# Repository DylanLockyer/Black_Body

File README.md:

# Black Body Controller
[USER MANUAL](Documentation/README.md)

## Overview
This project controls and monitors a black body heater module mounted to the 4K stage of a cryostat. It is split into two custom PCBs: a heater control board built around an ESP32 (current source, voltage/current sensing, PID control, and a self-hosted web interface) and a temperature sensor board built around an STM32G4 for reading from a germanium temperature sensor for ranges from 0.3 to 100 kelvin (high-precision, low-noise excitation and readout for temperature probes). The two boards communicate over SPI, with the ESP32 acting as the master controller and network-facing interface.

## Project Goals
- Heat the black body module (4x 10Ω heaters in series, 40Ω equivalent) from the cryostat's 4K stage to temperatures above 80K, with closed-loop PID control.
- Accurately measure temperature across the cryogenic range using a Germanium RTD (LakeShore GR-300-AA).
- Provide low-noise, precisely switchable current excitation (10nA to 1mA) and high-resolution (24-bit) voltage/current measurement for sensor readout.
- Expose a self-hosted web interface (over WiFi) for live monitoring and control of both heating and measurement, with no external software required.

## Documentation
- [Heater Control PCB](Circuit%20Boards/Black_Body_Heater_Control_PCB/README.md) — heater current source, voltage/current sensing, and power supply design.
- [Temperature Sensor PCB](Circuit%20Boards/Black_Body_Temperature_Sensor_PCB/README.md) — sensor excitation, precision measurement, and isolation design.
- [ESP32 Firmware](Firmware/ESP32_heater/README.md) — heater PID control, SPI link to the sensor board, and the web interface.
- [STM32 Firmware](Firmware/stm32_black_body/README.md) — sensor excitation control, ADC readout, and the SPI link to the ESP32.
- [Device Usage Guide](Documentation/README.md) — how to power up, connect to, and operate the device.

## Repository Organization
**Circuit Boards:** KiCad source files and manufacturing/gerber files for both PCBs.

**Firmware:** ESP32 (PlatformIO) heater control firmware and STM32 (STM32CubeIDE) sensor readout firmware.

**Documentation:** Images, schematics, and the device usage guide.

**Simulations:** LTspice and PSpice simulations used to validate circuit designs before ordering.

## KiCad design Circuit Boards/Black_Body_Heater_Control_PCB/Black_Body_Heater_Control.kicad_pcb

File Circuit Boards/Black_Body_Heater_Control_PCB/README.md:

# Black Body Heater Control PCB

Two-layer circuit board carrying the ESP32 microcontroller and all heater control electronics: current source, voltage/current sensing, and power supply. See the [firmware README](../../Firmware/ESP32_heater/README.md) for how this board is driven, and the [root README](../../README.md) for overall project context.

Schematic: [Black_Body_Heater_Control_Schematic.pdf](../Black_Body_Heater_Control_Schematic.pdf)

## Microcontroller
An ESP32 was chosen for its high pin count and WiFi support, letting it self-host a web page for displaying readings and controlling the heater. It interfaces with the [temperature sensor board](../Black_Body_Temperature_Sensor_PCB/README.md) over SPI (3 CS lines for 3 temperature probes). The microcontroller is programmed over USB, with exposed pads for UART programming as a fallback. Board-to-board interfacing uses Molex connectors (504050-0891 for the SPI link) since they could be sampled for free.

## Heater Controller
The heater is 4x 10Ω resistors in series (40Ω total). A maximum output power of 10W requires a peak 12V at 0.3A, measured with a shunt resistor + amplifier (current) and a voltage divider (voltage), both read by the ESP32's internal 12-bit ADC. This gives a theoretical current step of 100µA (max 0.66A range) and a voltage step of 8mV (max 36V range).

The original design used an N-channel MOSFET with PWM to control heater voltage. Due to concerns about PWM noise interfering with the sensor board's measurements, this was replaced with an analog current source instead.

Output current vs. input voltage for the analog current source. A BJT and op-amp generate the current output, driven by a DAC that the microcontroller controls.

## Shunt Current Measurement
The shunt resistor is 100mΩ with a 50V/V amplifier gain, giving 2.5V output at 0.5A and 0.25V at 0.05A. A low-pass filter on the amplifier output is largely unnecessary now that PWM isn't used, but is kept (with an easy jumper to bypass it) in case it's needed. Simulated filtering of a 10% duty cycle, 10kHz PWM signal on 20V is shown below:

## Power Source
The board receives 12V from an external power supply. A buck converter steps this down to 5V at 2A, followed by an LDO to 3.3V for a clean, low-noise supply to the microcontroller and ADC. \
**Revision 1:** Changed buck converter to newer module as the rev 0 as it broke and fried both boards.

## Simulation
Heater and buck converter behavior were validated in PSpice before layout (see [Simulations/Heater_Controller_PCB](../../Simulations/Heater_Controller_PCB)):

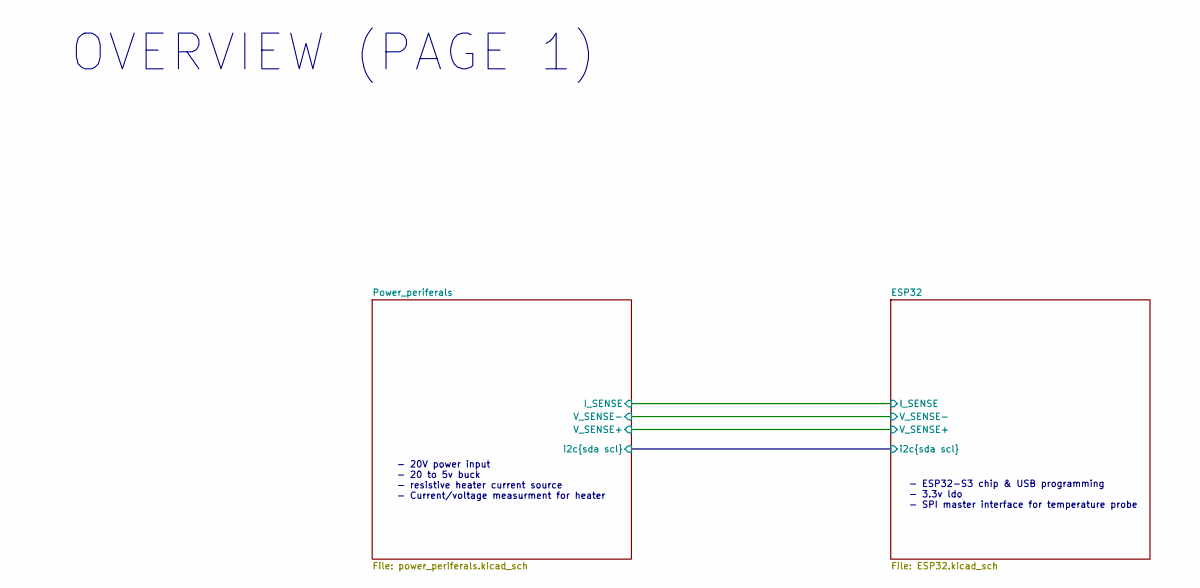
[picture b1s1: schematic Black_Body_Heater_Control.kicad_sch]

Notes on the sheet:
OVERVIEW (PAGE 1)
- ESP32-S3 chip & USB programming - 3.3v ldo - SPI master interface for temperature probe
- 20V power input - 20 to 5v buck - resistive heater current source - Current/voltage measurment for heater

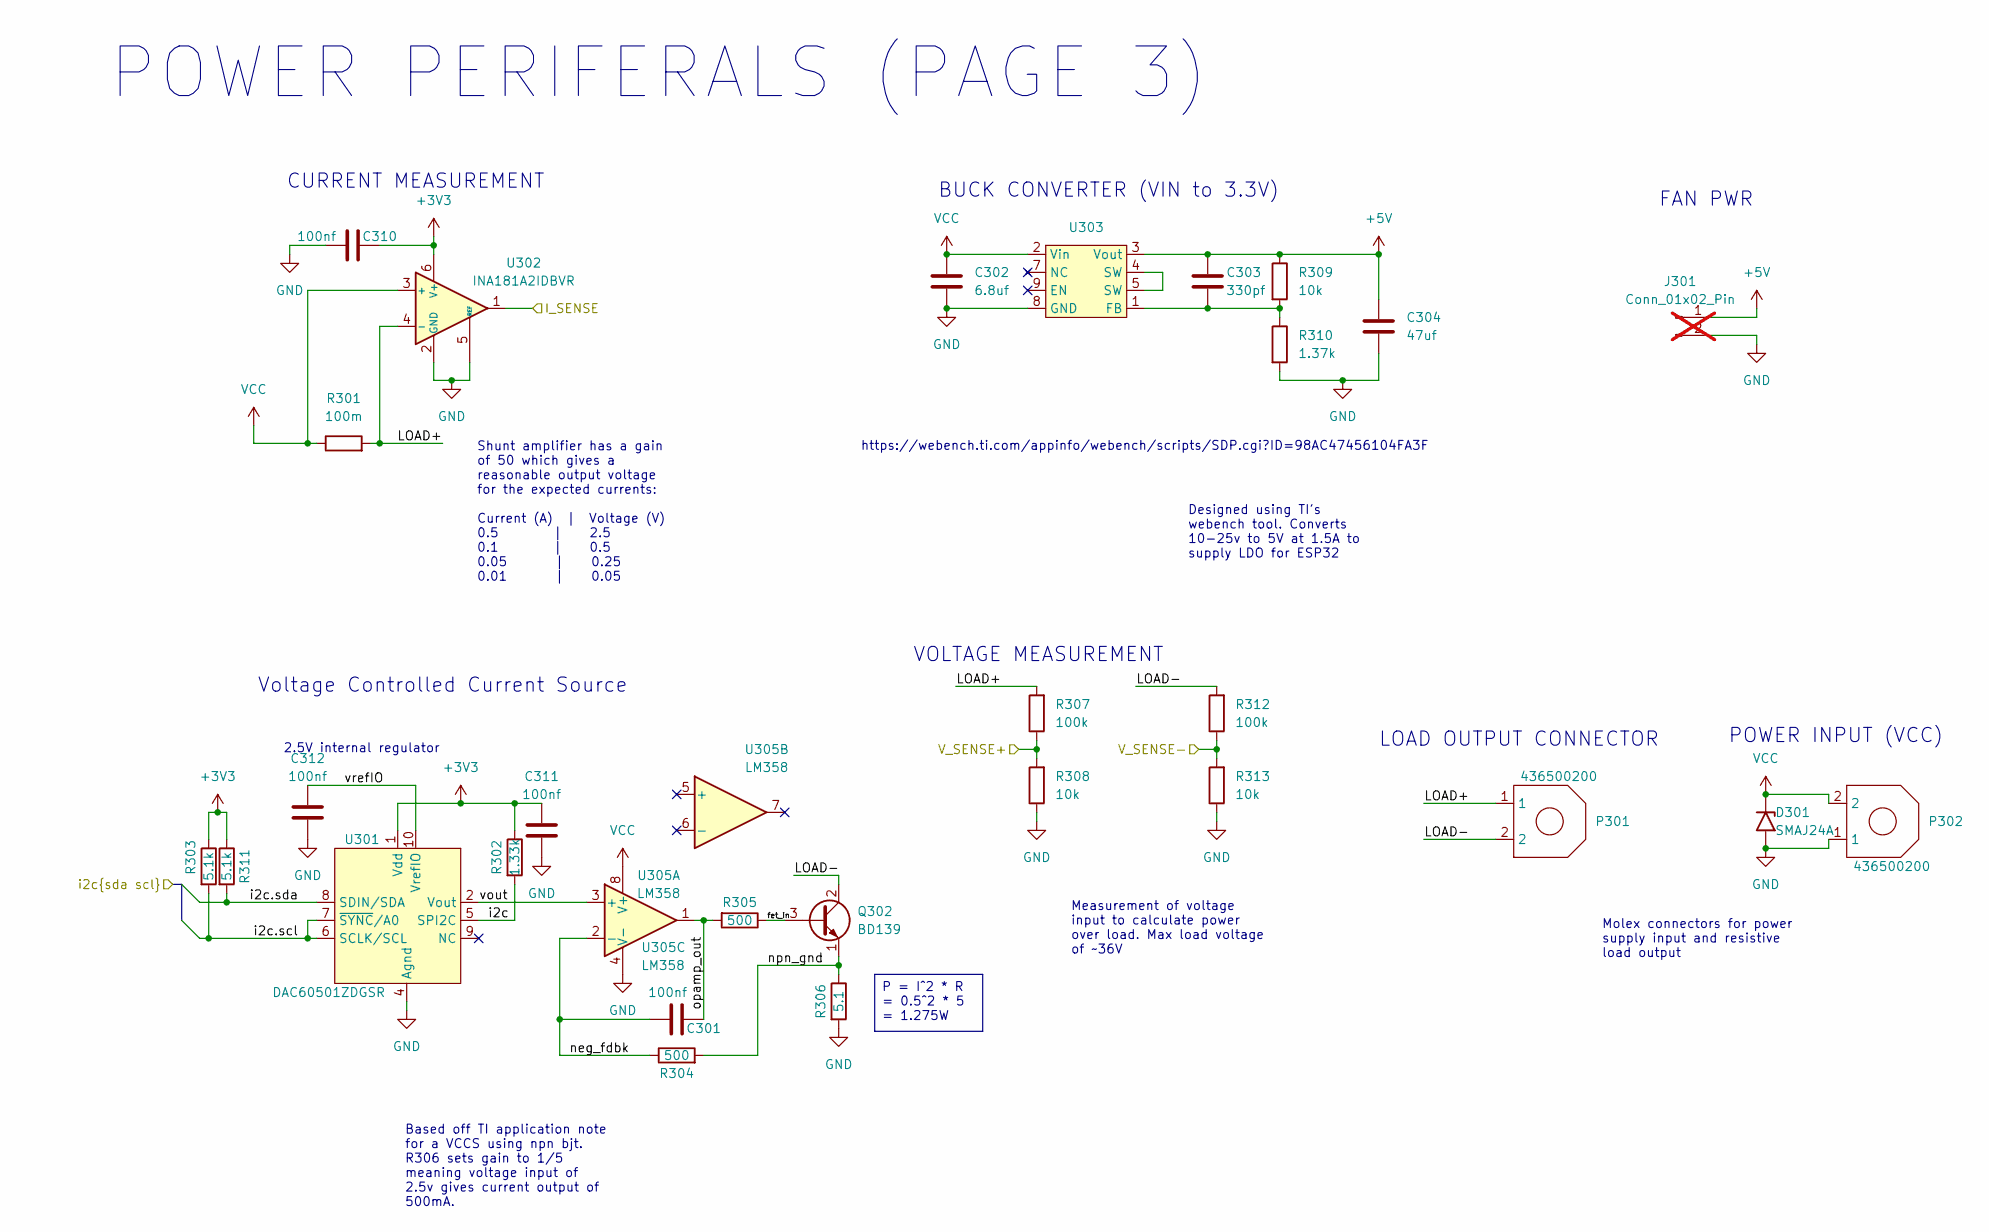
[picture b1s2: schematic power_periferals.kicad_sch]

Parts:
C301, C310, C311, C312: 100nf; C_0603_1608Metric; MPN CL10B104KB8NNNC
C302: 6.8uf; C_0603_1608Metric; MPN C1608X5R1E685K080AC
C303: 330pf; C_0603_1608Metric; MPN C0603C331J5GACTU
C304: 47uf; C_1210_3225Metric; MPN GRM32EC81C476KE15L
D301: SMAJ24A; D_SMA; MPN SMAJ24A
J301: Conn_01x02_Pin; PinHeader_1x02_P1.27mm_Vertical; not fitted
P301, P302: 436500200; 436500200 2-pin; MPN 436500200
Q302: BD139; TO-126-3_Vertical; MPN BD139
R301: 100m; R_0805_2012Metric; MPN RCWE0805R100FKEA
R302: 1.33k; R_0603_1608Metric; MPN ERA-3AEB1331V
R303, R311: 5.1k; R_0402_1005Metric; MPN RT0402BRD075K1L
R304, R305: 500; R_0603_1608Metric; MPN ERA-3AEB4990V
R306: 5.1; R_2512_6332Metric; MPN CRM2512-FX-5R10ELF
R307, R312: 100k; R_0603_1608Metric; MPN ERA-3AEB104V
R308, R309, R313: 10k; R_0603_1608Metric; MPN ERA-3AEB103V
R310: 1.37k; R_0603_1608Metric; MPN ERJ-3EKF1371V
U301: DAC60501ZDGSR; TSSOP-10_3x3mm_P0.5mm; MPN DAC60501ZDGSR
U302: INA181A2IDBVR; SOT-23-6; MPN INA181A2IDBVR
U303: TPSM84209; MPN TPSM84209RKHR
U305: LM358; SOIC-8_3.9x4.9mm_P1.27mm; MPN LM358BAIDR

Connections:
+3V3: C310.2, C311.2, R302.1, R303.1, R311.1, U301.1 (Vdd), U302.6 (V+); also elsewhere on the board
+5V: C303.1, C304.1, J301.1, R309.1, U303.3 (Vout); also elsewhere on the board
/ESP32/I_SENSE: U302.1; also elsewhere on the board
/ESP32/V_SENSE+: R307.1, R308.2; also elsewhere on the board
/ESP32/V_SENSE-: R312.1, R313.2; also elsewhere on the board
/ESP32/i2c.scl: R303.2, U301.6 (SCLK/SCL), U301.7 (~SYNC/A0); also elsewhere on the board
/ESP32/i2c.sda: R311.2, U301.8 (SDIN/SDA); also elsewhere on the board
/Power_periferals/LOAD+: P301.1, R301.2, R307.2, U302.4 (-)
/Power_periferals/LOAD-: P301.2, Q302.2 (C), R312.2
/Power_periferals/fet_in: Q302.3 (B), R305.1
/Power_periferals/i2c: R302.2, U301.5 (SPI2C)
/Power_periferals/neg_fdbk: C301.1, R304.1, U305.2 (-)
/Power_periferals/npn_gnd: Q302.1 (E), R304.2, R306.1
/Power_periferals/opamp_out: C301.2, R305.2, U305.1
/Power_periferals/vout: U301.2 (Vout), U305.3 (+)
/Power_periferals/vrefIO: C312.2, U301.10 (VrefIO)
GND: C302.2, C304.2, C310.1, C311.1, C312.1, D301.2 (A2), J301.2, P302.1, R306.2, R308.1, R310.2, R313.1, U301.4 (Agnd), U302.2 (GND), U302.5 (REF), U303.8 (GND), U305.4 (V-); also elsewhere on the board
unnamed: C303.2, R309.2, R310.1, U303.1 (FB)
unnamed: U303.4 (SW), U303.5 (SW)
VCC: C302.1, D301.1 (A1), P302.2, R301.1, U302.3 (+), U303.2 (Vin), U305.8 (V+)

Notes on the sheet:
https://webench.ti.com/appinfo/webench/scripts/SDP.cgi?ID=98AC47456104FA3F
POWER INPUT (VCC)
BUCK CONVERTER (VIN to 3.3V)
VOLTAGE MEASUREMENT
FAN PWR
POWER PERIFERALS (PAGE 3)
2.5V internal regulator
Voltage Controlled Current Source
CURRENT MEASUREMENT
LOAD OUTPUT CONNECTOR
Molex connectors for power supply input and resistive load output
Designed using TI's webench tool. Converts 10-25v to 5V at 1.5A to supply LDO for ESP32
Shunt amplifier has a gain of 50 which gives a reasonable output voltage for the expected currents: Current (A) | Voltage (V) 0.5 | 2.5 0.1 | 0.5 0.05 | 0.25 0.01 | 0.05
Measurement of voltage input to calculate power over load. Max load voltage of ~36V
P = I^2 * R = 0.5^2 * 5 = 1.275W
Based off TI application note for a VCCS using npn bjt. R306 sets gain to 1/5 meaning voltage input of 2.5v gives current output of 500mA.

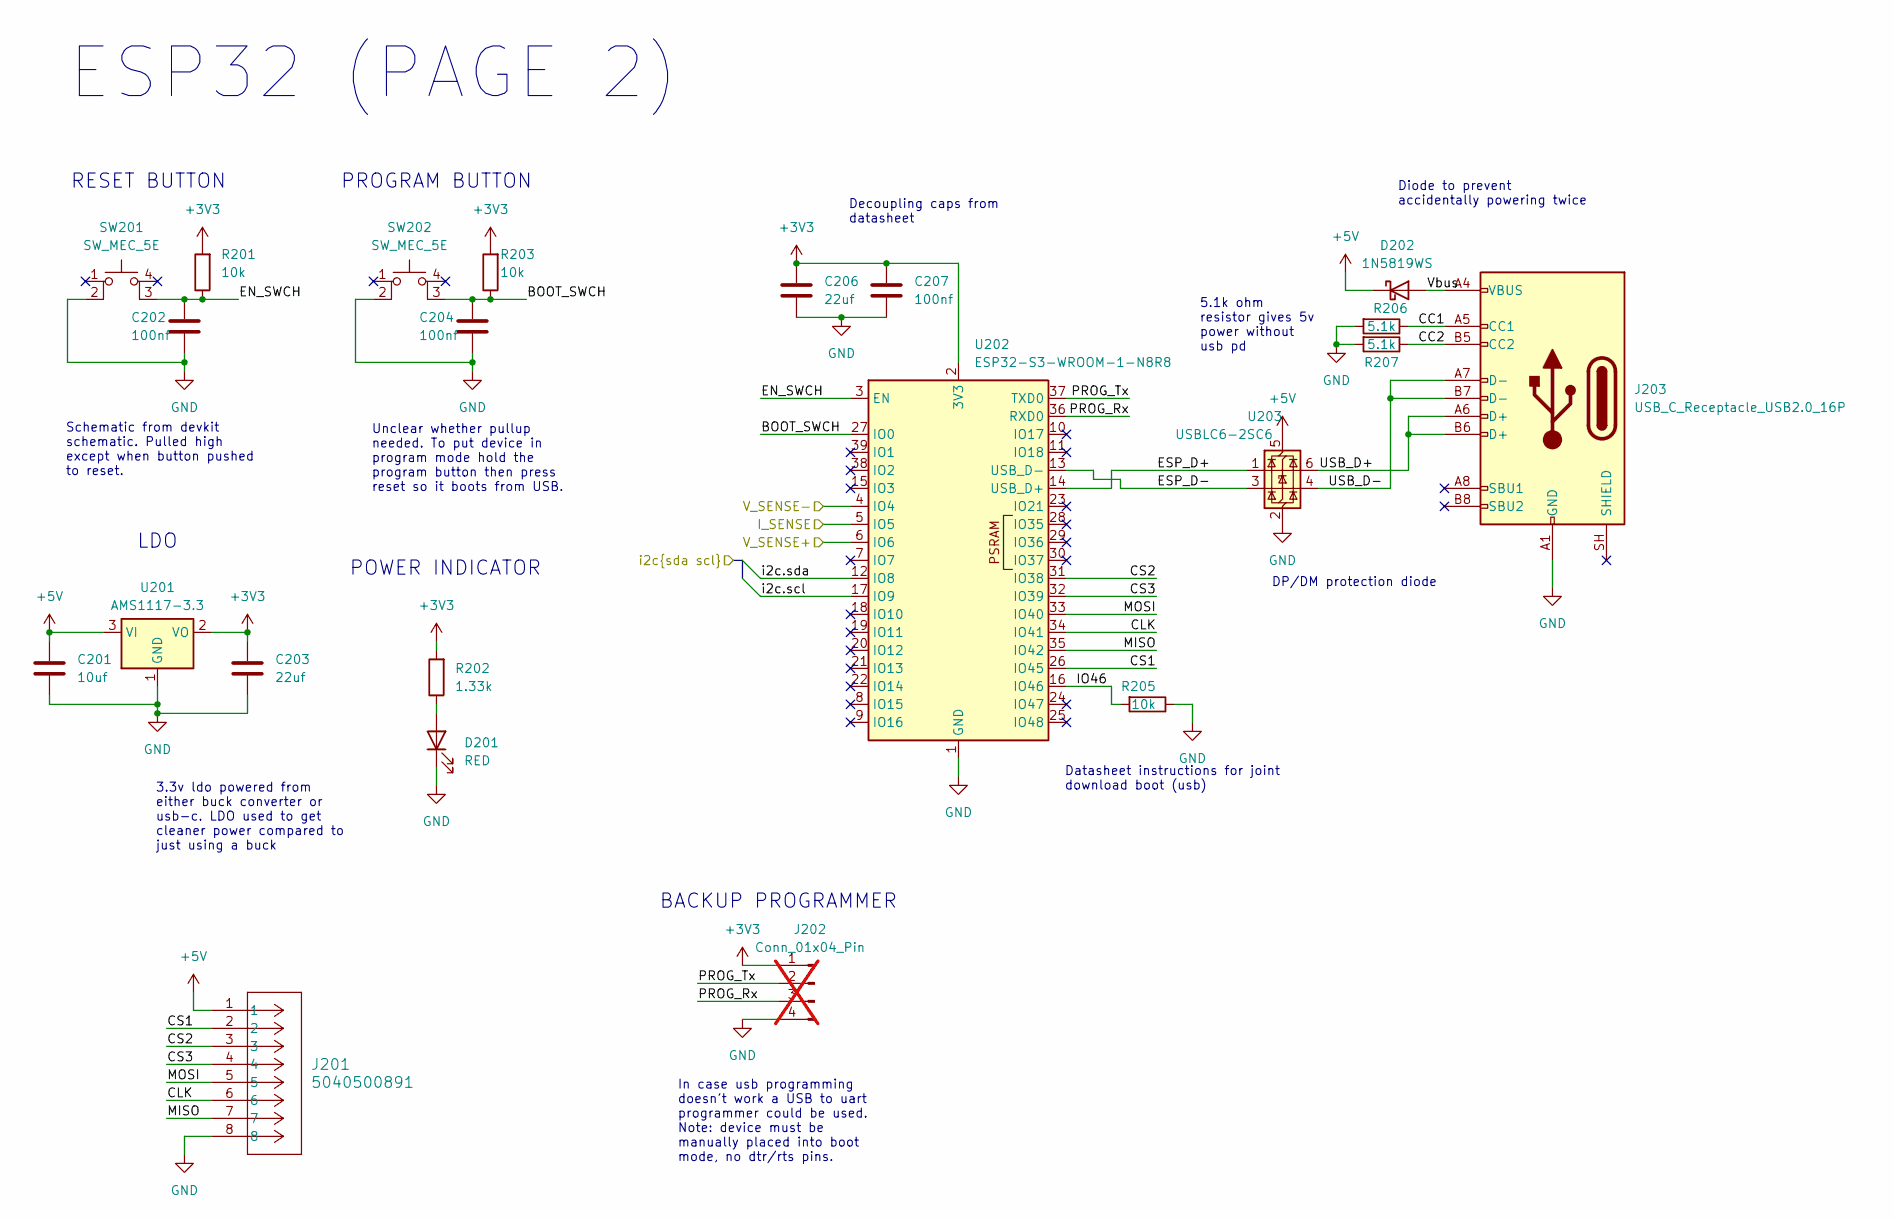
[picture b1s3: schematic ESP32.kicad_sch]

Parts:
C201: 10uf; C_0603_1608Metric; MPN GRM188R6YA106MA73D
C202, C204, C207: 100nf; C_0603_1608Metric; MPN CL10B104KB8NNNC
C203, C206: 22uf; C_0603_1608Metric; MPN CL10A226MP8NUNE
D201: RED; LED_0603_1608Metric; MPN LTST-C191KRKT
D202: 1N5819WS; D_SOD-323; MPN 1N5819WS
J201: 5040500891; CONN_5040500891_MOL; MPN 5040500891
J202: Conn_01x04_Pin; PinHeader_1x04_P1.00mm_Vertical; not fitted
J203: USB_C_Receptacle_USB2.0_16P; UJ20-C-H-G-SMT-1-P16-TR; MPN UJ20-C-H-G-SMT-1-P16-TR
R201, R203, R205: 10k; R_0603_1608Metric; MPN ERA-3AEB103V
R202: 1.33k; R_0603_1608Metric; MPN ERA-3AEB1331V
R206, R207: 5.1k; R_0402_1005Metric; MPN RT0402BRD075K1L
SW201, SW202: SW_MEC_5E; 430471035826; MPN SW_MEC_5E
U201: AMS1117-3.3; SOT-223-3_TabPin2; MPN AMS1117-3.3
U202: ESP32-S3-WROOM-1-N8R8; ESP32-S3-WROOM-1; MPN ESP32-S3-WROOM-1-N8R8
U203: USBLC6-2SC6; SOT-23-6; MPN USBLC6-2SC6

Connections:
+3V3: C203.1, C206.1, C207.1, J202.1, R201.2, R202.2, R203.2, U201.2 (VO), U202.2 (3V3); also elsewhere on the board
+5V: C201.1, D202.1 (K), J201.1, U201.3 (VI), U203.5 (VBUS); also elsewhere on the board
/ESP32/BOOT_SWCH: C204.1, R203.1, SW202.3 (K), U202.27 (IO0)
/ESP32/CC1: J203.A5 (CC1), R206.1
/ESP32/CC2: J203.B5 (CC2), R207.1
/ESP32/CLK: J201.6, U202.34 (IO41)
/ESP32/CS1: J201.2, U202.26 (IO45)
/ESP32/CS2: J201.3, U202.31 (IO38)
/ESP32/CS3: J201.4, U202.32 (IO39)
/ESP32/EN_SWCH: C202.1, R201.1, SW201.3 (K), U202.3 (EN)
/ESP32/ESP_D+: U202.14 (USB_D+), U203.1 (I/O1)
/ESP32/ESP_D-: U202.13 (USB_D-), U203.3 (I/O2)
/ESP32/IO46: R205.2, U202.16 (IO46)
/ESP32/I_SENSE: U202.5 (IO5); also elsewhere on the board
/ESP32/MISO: J201.7, U202.35 (IO42)
/ESP32/MOSI: J201.5, U202.33 (IO40)
/ESP32/PROG_Rx: J202.3, U202.36 (RXD0)
/ESP32/PROG_Tx: J202.2, U202.37 (TXD0)
/ESP32/USB_D+: J203.A6 (D+), J203.B6 (D+), U203.6 (I/O1)
/ESP32/USB_D-: J203.A7 (D-), J203.B7 (D-), U203.4 (I/O2)
/ESP32/V_SENSE+: U202.6 (IO6); also elsewhere on the board
/ESP32/V_SENSE-: U202.4 (IO4); also elsewhere on the board
/ESP32/Vbus: D202.2 (A), J203.A4 (VBUS), J203.A9 (VBUS), J203.B4 (VBUS), J203.B9 (VBUS)
/ESP32/i2c.scl: U202.17 (IO9); also elsewhere on the board
/ESP32/i2c.sda: U202.12 (IO8); also elsewhere on the board
GND: C201.2, C202.2, C203.2, C204.2, C206.2, C207.2, D201.1 (K), J201.8, J202.4, J203.A1 (GND), J203.A12 (GND), J203.B1 (GND), J203.B12 (GND), R205.1, R206.2, R207.2, SW201.2, SW202.2, U201.1 (GND), U202.1 (GND), U202.40 (GND), U202.41 (GND), U203.2 (GND); also elsewhere on the board
unnamed: D201.2 (A), R202.1

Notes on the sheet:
POWER INDICATOR
RESET BUTTON
PROGRAM BUTTON
BACKUP PROGRAMMER
ESP32 (PAGE 2)
LDO
3.3v ldo powered from either buck converter or usb-c. LDO used to get cleaner power compared to just using a buck
Schematic from devkit schematic. Pulled high except when button pushed to reset.
Unclear whether pullup needed. To put device in program mode hold the program button then press reset so it boots from USB.
Datasheet instructions for joint download boot (usb)
Diode to prevent accidentally powering twice
Decoupling caps from datasheet
5.1k ohm resistor gives 5v power without usb pd
DP/DM protection diode
In case usb programming doesn't work a USB to uart programmer could be used. Note: device must be manually placed into boot mode, no dtr/rts pins.

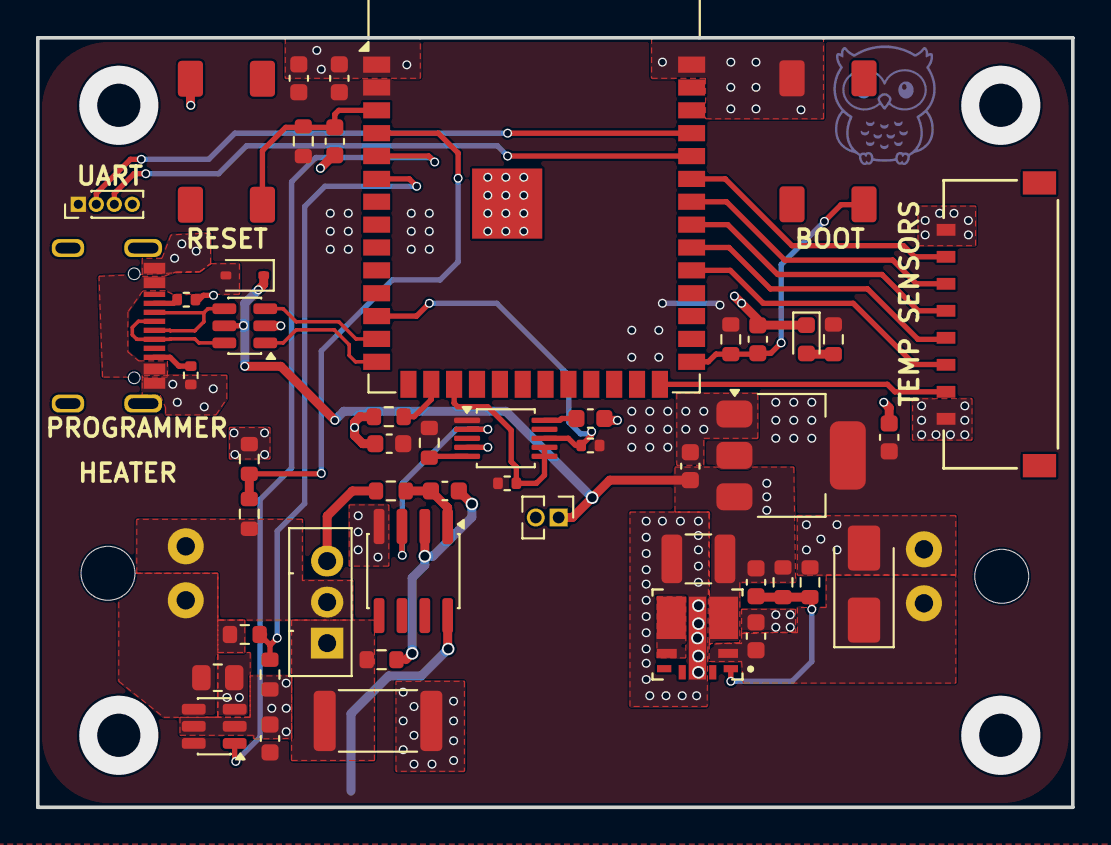
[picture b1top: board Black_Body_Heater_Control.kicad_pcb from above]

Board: 2 copper layers, 57.5 x 42.8 mm, 51 parts (0 on the bottom side), 39 nets.

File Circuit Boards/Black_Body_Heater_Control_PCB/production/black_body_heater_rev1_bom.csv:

Designator,Footprint,Quantity,Value,LCSC Part #
C201,0603,1,10uf,GRM188R6YA106MA73D
"C202, C204, C207, C301, C310, C311, C312",0603,7,100nf,CL10B104KB8NNNC
"C203, C206",0603,2,22uf,CL10A226MP8NUNE
C302,0603,1,6.8uf,C1608X5R1E685K080AC
C303,0603,1,330pf,C0603C331J5GACTU
C304,1210,1,47uf,GRM32EC81C476KE15L
D201,0603,1,RED,LTST-C191KRKT
D202,D_SOD-323,1,1N5819WS,1N5819WS
D301,D_SMA,1,SMAJ24A,SMAJ24A
J201,CONN_5040500891_MOL,1,5040500891,5040500891
J203,UJ20-C-H-G-SMT-1-P16-TR,1,USB_C_Receptacle_USB2.0_16P,UJ20-C-H-G-SMT-1-P16-TR
"P301, P302",436500200 2-pin,2,436500200,436500200
Q302,TO-126-3_Vertical,1,BD139,BD139
"R201, R203, R205, R308, R309, R313",0603,6,10k,ERA-3AEB103V
"R202, R302",0603,2,1.33k,ERA-3AEB1331V
"R206, R207, R303, R311",0402,4,5.1k,RT0402BRD075K1L
R301,0805,1,100m,RCWE0805R100FKEA
"R304, R305",0603,2,500,ERA-3AEB4990V
R306,2512,1,5.1,CRM2512-FX-5R10ELF
"R307, R312",0603,2,100k,ERA-3AEB104V
R310,0603,1,1.37k,ERJ-3EKF1371V
"SW201, SW202",430471035826,2,SW_MEC_5E,SW_MEC_5E
U201,SOT-223-3_TabPin2,1,AMS1117-3.3,AMS1117-3.3
U202,ESP32-S3-WROOM-1,1,ESP32-S3-WROOM-1-N8R8,ESP32-S3-WROOM-1-N8R8
U203,SOT-23-6,1,USBLC6-2SC6,USBLC6-2SC6
U301,TSSOP-10_3x3mm_P0.5mm,1,DAC60501ZDGSR,DAC60501ZDGSR
U302,SOT-23-6,1,INA181A2IDBVR,INA181A2IDBVR
U303,TPSM84209,1,~,TPSM84209RKHR
U305,SOIC-8_3.9x4.9mm_P1.27mm,1,LM358,LM358BAIDR

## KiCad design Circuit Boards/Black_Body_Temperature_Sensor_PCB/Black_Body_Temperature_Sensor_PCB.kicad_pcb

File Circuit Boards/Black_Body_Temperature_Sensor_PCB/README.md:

# Black Body Temperature Sensor PCB

Six-layer circuit board that reads temperature from Germanium RTD sensors and Silicon diode sensors. See the [firmware README](../../Firmware/stm32_black_body/README.md) for how this board is driven, and the [root README](../../README.md) for overall project context.

Schematic/board renders: [Black_Body_Temperature_Sensor_Schematic.pdf](../../Documentation/Black_Body_Temperature_Sensor_Schematic.pdf), [Black_Body_Temperature_Sensor_PCB.pdf](../../Documentation/Black_Body_Temperature_Sensor_PCB.pdf)

## Temperature Probe Readers
The board must support both Germanium sensors (LakeShore GR-300-AA) and Silicon diode sensors (LakeShore DT-670A1-CU), which are both 4-wire sensors: current is sourced over 2 wires (I+/I-) and voltage is read over the other 2 (V+/V-) so the voltage drop across the lead wires isn't included in the measurement.

Two LakeShore temperature probe readers were used as reference:

**Model 224:** Accurate to 0.3K with DC current from 100nA to 1mA. Ability to source both positive and negative current allows EMF voltages to be eliminated.

**Model 372:** Accurate to 0.05K with AC current as low as 10pA to eliminate self-heating at extremely low temperatures (power levels in attowatts, 10⁻¹⁸W). Significantly more complex to implement and unnecessary for our sensors, which don't go below 0.3K.

The Model 224 was used as the primary reference since this application won't go below 4K, and it supports almost the full range of the GR-300-AA and the full range of the DT-670A1-CU (down to 1.4K).

## DT-670A1-CU Sensor

Silicon diode temperature sensor, 1.4K to 420K range. Requires a constant excitation of 10µA ± 0.1%; the voltage across it ranges from 1.64V at 1.4K to 0.560V at 305K.

## GR-300-AA Sensor

Germanium temperature sensor, 0.3K to 100K range. Resistance varies logarithmically with temperature, from 35180Ω at 0.3K to 2.716Ω at 100K. Below 1K, excitation should be limited (LakeShore recommends 63µV; the Model 224 uses 3600µV at 0.3K to 900µV at 1K) since thermal mass is very small and self-heating matters more. Above 1K, excitation should stay under 10mV; the Model 224 sources 100nA to 1mA to keep the voltage under that limit.

## My Implementation
- Current excitation from 10nA to 1mA, DC, switchable direction.
- High-precision instrumentation amplifier for I+/I- sensor lead current measurement.
- Voltage measurement precise across 1mV to 10mV, since below 1K the signal can't go lower than ~0.9mV (10nA) and above 1K self-heating matters less.
- 24-bit ADC for both current and voltage; galvanic isolation between the digital and analog side is manually bypassed as it was causing issues and the same power supply is used for both digital and analog sides.
- Low-noise, high common-mode-rejection amplifiers to bring small signals up to reasonable voltage levels.

## Clean Voltage Supply
The board takes in a clean +12V, low-pass filtered. An LTC3260 splits the rail into +5V and -5V. The +5V rail is regulated to +3.3V with an LT3042EMSE, and the -5V rail similarly with an LT3094, for extra-clean supplies.

The LTC3260 could not be simulated (a common issue with its SPICE model), but the 3.3V regulator stages were simulated:

## Current Sources
Target outputs: 10nA, 100nA, 1µA, 10µA, 100µA, 1mA, split into two circuits (below 1µA and above/equal to 1µA).

Greater-than-1µA source, using the TI LM334 per its application note. Different current outputs are selected by switching resistors R1 & R3 with high-precision analog switches.

Less-than-1µA source, also using the LM334 but following an Analog Devices example schematic with an instrumentation op-amp to reach the 10nA range (confirmed by simulation). Analog switches again select the current level.

## Voltage Measurement
The Germanium sensors produce 0.5mV to 5mV at the given excitation currents. The signal is buffered by an OPA376 (10pA bias current), then fed to a differential instrumentation amplifier (AD8421ARZ, 200x gain), then into one of the 4 channels of a 24-bit ADC (ADS131M04). The ADC communication is isolated from the microcontroller to keep the analog and digital grounds separate.

## Current Measurement
Measured via the shunt method, using the same voltage-measurement chain to read the voltage drop across a 5Ω, 500Ω, or 33kΩ shunt (selected with analog switches).

## Switching Current Direction
The same analog switches (TMUX1112PWR, 3pA noise injection) reverse current direction between measurements to cancel out EMF voltages induced by dissimilar metals in the sensor leads.

## Digital Section
Built around the STM32G4. It has a 5V-tolerant SPI interface for talking to the [heater control board](../Black_Body_Heater_Control_PCB/README.md), and a USB 2.0 interface for programming and future use with a PC application. Either connection can supply power, with protection against both being connected simultaneously. An I2C breakout is provided for future expansion. All GPIOs driving the analog-section switches pass through a PI filter first to give a slow ramp-up and limit noise:

## Stackup
Six layers, chosen to simplify grounding, with ENIG surface finish:

```
Analog
Gnd
+3.3V
-3.3V
Gnd
Mixed signal
```

The two 3.3V layers also carry small digital 3.3V and GND traces to the analog switches. The bottom layer is primarily digital switch routing, with some small analog jumps.

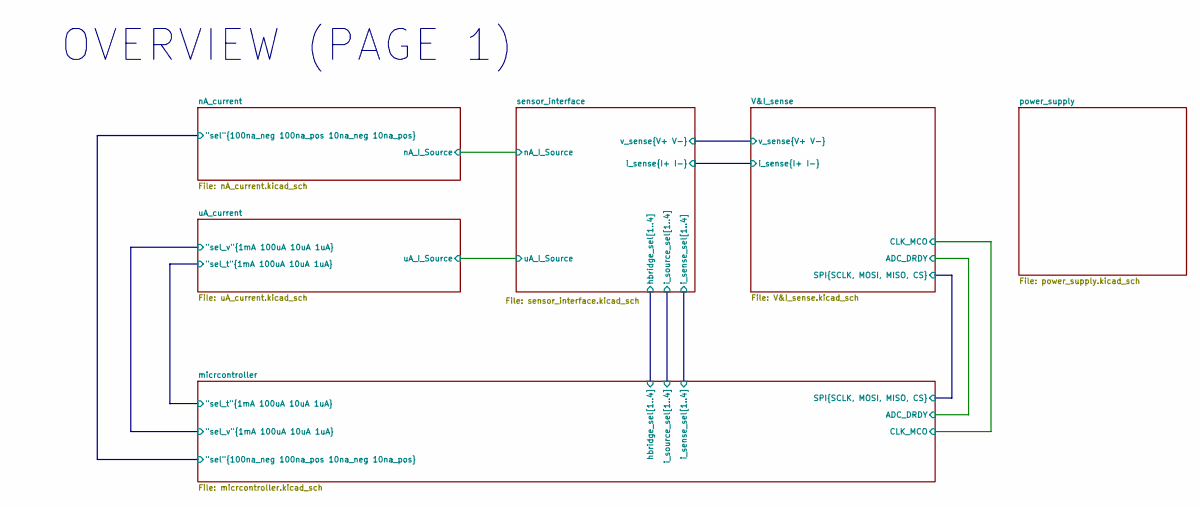
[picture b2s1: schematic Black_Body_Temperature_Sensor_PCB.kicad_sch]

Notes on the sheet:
OVERVIEW (PAGE 1)

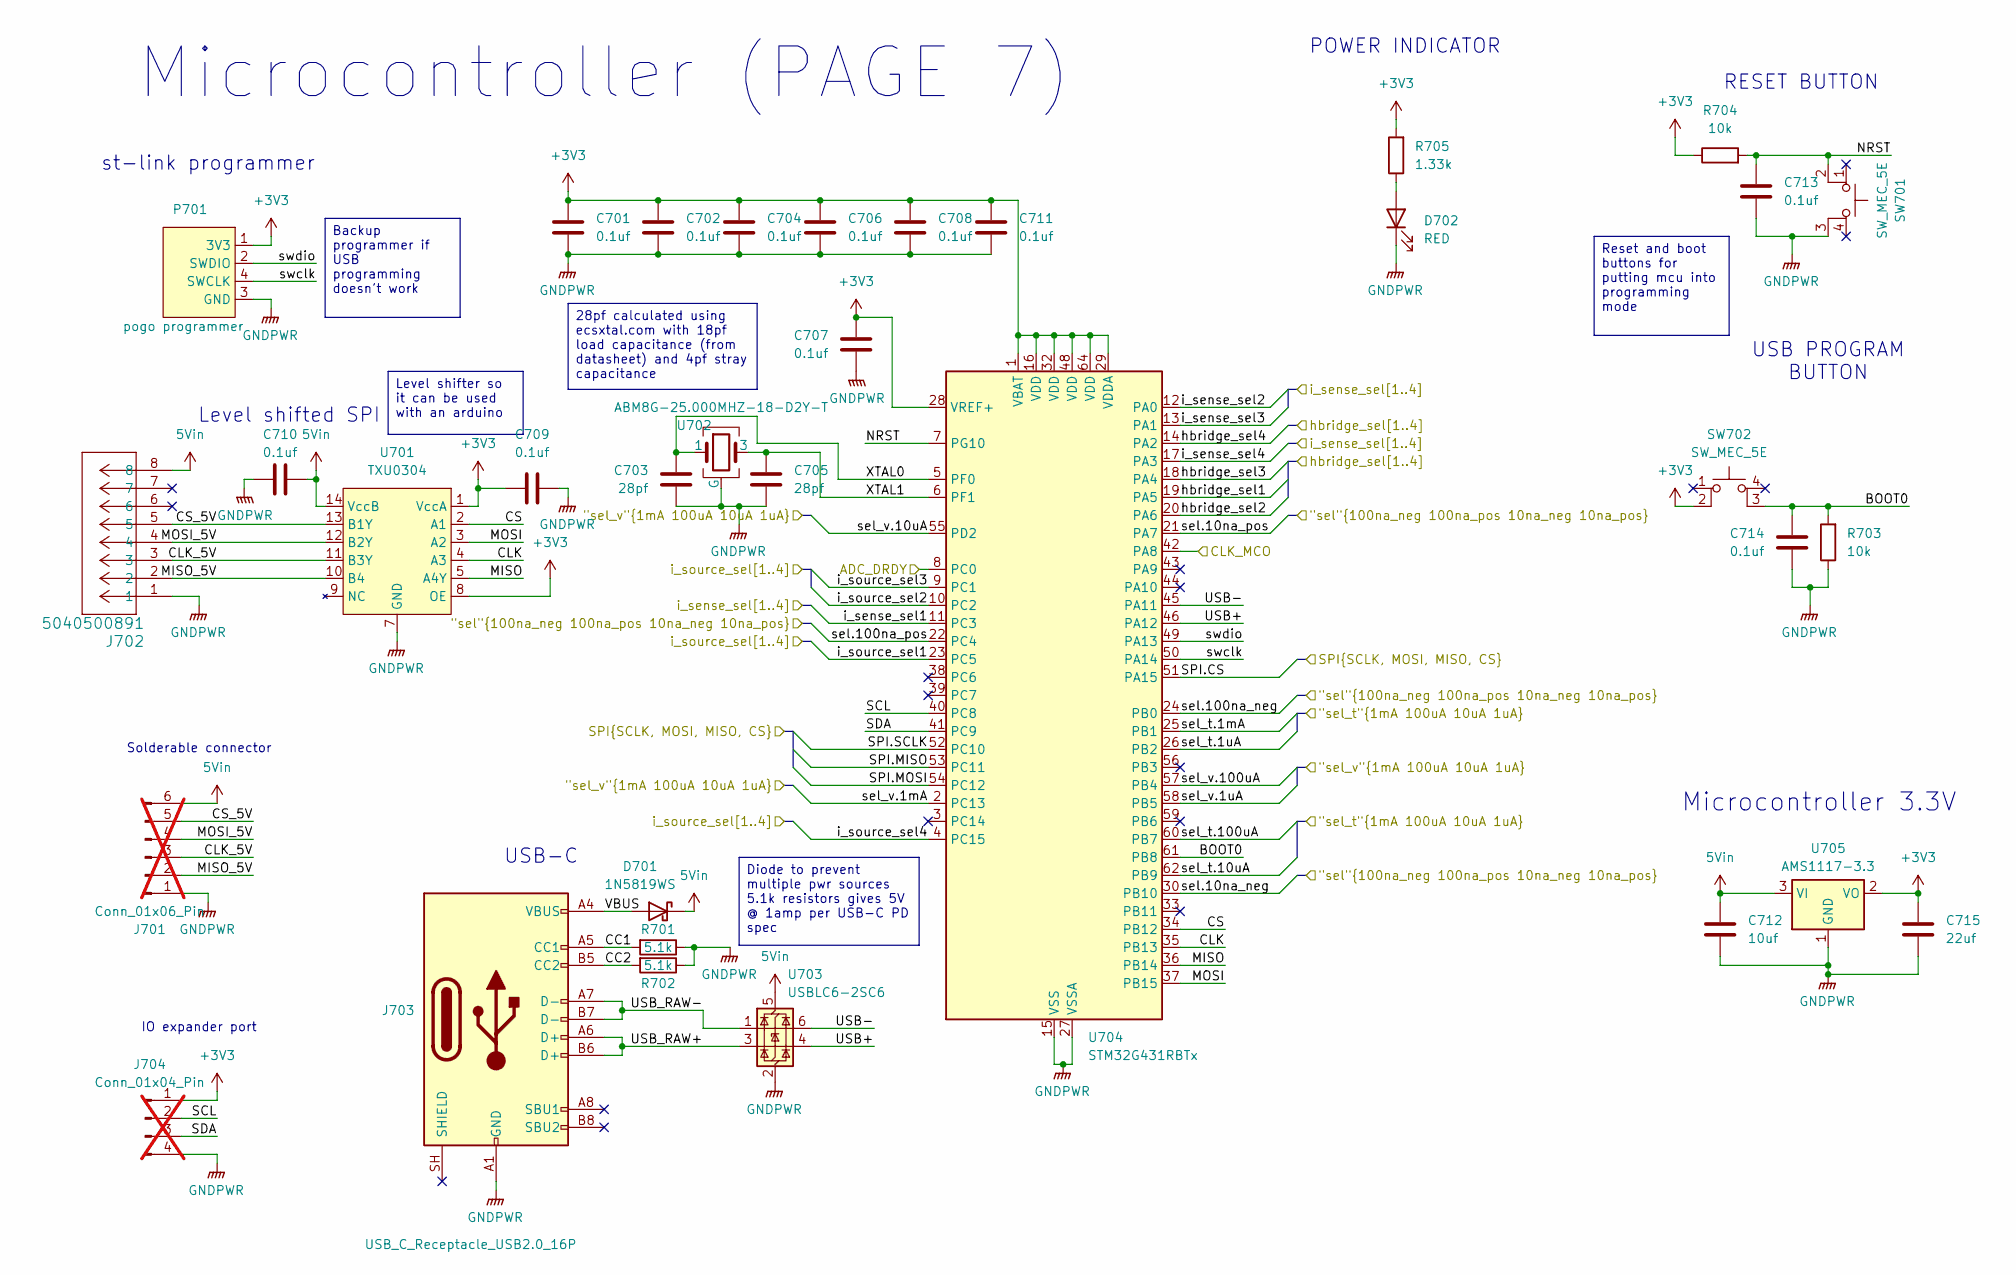
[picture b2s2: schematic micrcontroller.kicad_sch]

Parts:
C701, C702, C704, C706, C707, C708, C709, C710, C711, C713, C714: 0.1uf; C_0603_1608Metric; MPN CL10B104KB8NNNC
C703, C705: 28pf; C_0603_1608Metric; MPN CL10C270JB8NNNC
C712: 10uf; C_0603_1608Metric; MPN GRM188R6YA106MA73D
C715: 22uf; C_0603_1608Metric; MPN CL10A226MP8NUNE
D701: 1N5819WS; D_SOD-323; MPN 1N5819WS
D702: RED; LED_0603_1608Metric; MPN LTST-C191KRKT
J701: Conn_01x06_Pin; PinHeader_1x06_P2.54mm_Vertical; not fitted
J702: 5040500891; CONN_5040500891_MOL; MPN 5040500891
J703: USB_C_Receptacle_USB2.0_16P; UJ20-C-H-G-SMT-1-P16-TR; MPN UJ20-C-H-G-SMT-1-P16-TR
J704: Conn_01x04_Pin; PinHeader_1x04_P2.54mm_Vertical; not fitted
P701: pogo programmer; pogo_programmer
R701, R702: 5.1k; R_0402_1005Metric; MPN RT0402BRD075K1L
R703, R704: 10k; R_0603_1608Metric; MPN ERA-3AEB103V
R705: 1.33k; R_0603_1608Metric; MPN ERA-3AEB1331V
SW701, SW702: SW_MEC_5E; 430471035826; MPN 430471035826
U701: TXU0304; TSSOP-14_4.4x5mm_P0.65mm; MPN TXU0304PWR
U702: ABM8G-25.000MHZ-18-D2Y-T; MPN ABM8G-25.000MHZ-18-D2Y-T
U703: USBLC6-2SC6; SOT-23-6; MPN USBLC6-2SC6c
U704: STM32G431RBTx; LQFP-64_10x10mm_P0.5mm; MPN STM32G431RBT6
U705: AMS1117-3.3; SOT-223-3_TabPin2; MPN AMS1117-3.3

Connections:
5Vin: C710.1, C712.1, D701.1 (K), J701.6, J702.8, U701.14 (VccB), U703.5 (VBUS), U705.3 (VI)
+3V3: C701.1, C702.1, C704.1, C706.1, C707.1, C708.1, C709.1, C711.1, C715.1, J704.1, P701.1 (3V3), R704.1, R705.2, SW702.2, U701.1 (VccA), U701.8 (OE), U704.1 (VBAT), U704.16 (VDD), U704.28 (VREF+), U704.29 (VDDA), U704.32 (VDD), U704.48 (VDD), U704.64 (VDD), U705.2 (VO); also elsewhere on the board
/V&I_sense/ADC_DRDY: U704.8 (PC0); also elsewhere on the board
/V&I_sense/CLK_MCO: U704.42 (PA8); also elsewhere on the board
/V&I_sense/SPI.CS: U704.51 (PA15); also elsewhere on the board
/V&I_sense/SPI.MISO: U704.53 (PC11); also elsewhere on the board
/V&I_sense/SPI.MOSI: U704.54 (PC12); also elsewhere on the board
/V&I_sense/SPI.SCLK: U704.52 (PC10); also elsewhere on the board
/micrcontroller/BOOT0: C714.1, R703.2, SW702.3 (K), U704.61 (PB8)
/micrcontroller/CC1: J703.A5 (CC1), R701.2
/micrcontroller/CC2: J703.B5 (CC2), R702.2
/micrcontroller/CLK: U701.4 (A3), U704.35 (PB13)
/micrcontroller/CLK_5V: J701.3, J702.3, U701.11 (B3Y)
/micrcontroller/CS: U701.2 (A1), U704.34 (PB12)
/micrcontroller/CS_5V: J701.5, J702.5, U701.13 (B1Y)
/micrcontroller/MISO: U701.5 (A4Y), U704.36 (PB14)
/micrcontroller/MISO_5V: J701.2, J702.2, U701.10 (B4)
/micrcontroller/MOSI: U701.3 (A2), U704.37 (PB15)
/micrcontroller/MOSI_5V: J701.4, J702.4, U701.12 (B2Y)
/micrcontroller/NRST: C713.1, R704.2, SW701.2, U704.7 (PG10)
/micrcontroller/SCL: J704.2, U704.40 (PC8)
/micrcontroller/SDA: J704.3, U704.41 (PC9)
/micrcontroller/USB+: U703.4 (I/O2), U704.46 (PA12)
/micrcontroller/USB-: U703.6 (I/O1), U704.45 (PA11)
/micrcontroller/USB_RAW+: J703.A6 (D+), J703.B6 (D+), U703.3 (I/O2)
/micrcontroller/USB_RAW-: J703.A7 (D-), J703.B7 (D-), U703.1 (I/O1)
/micrcontroller/VBUS: D701.2 (A), J703.A4 (VBUS), J703.A9 (VBUS), J703.B4 (VBUS), J703.B9 (VBUS)
/micrcontroller/XTAL0: C703.1, U702.1, U704.5 (PF0)
/micrcontroller/XTAL1: C705.1, U702.3, U704.6 (PF1)
/micrcontroller/hbridge_sel1: U704.19 (PA5); also elsewhere on the board
/micrcontroller/hbridge_sel2: U704.20 (PA6); also elsewhere on the board
/micrcontroller/hbridge_sel3: U704.18 (PA4); also elsewhere on the board
/micrcontroller/hbridge_sel4: U704.14 (PA2); also elsewhere on the board
/micrcontroller/i_sense_sel1: U704.11 (PC3); also elsewhere on the board
/micrcontroller/i_sense_sel2: U704.12 (PA0); also elsewhere on the board
/micrcontroller/i_sense_sel3: U704.13 (PA1); also elsewhere on the board
/micrcontroller/i_sense_sel4: U704.17 (PA3); also elsewhere on the board
/micrcontroller/i_source_sel1: U704.23 (PC5); also elsewhere on the board
/micrcontroller/i_source_sel2: U704.10 (PC2); also elsewhere on the board
/micrcontroller/i_source_sel3: U704.9 (PC1); also elsewhere on the board
/micrcontroller/i_source_sel4: U704.4 (PC15); also elsewhere on the board
/micrcontroller/sel.10na_neg: U704.30 (PB10); also elsewhere on the board
/micrcontroller/sel.10na_pos: U704.21 (PA7); also elsewhere on the board
/micrcontroller/sel.100na_neg: U704.24 (PB0); also elsewhere on the board
/micrcontroller/sel.100na_pos: U704.22 (PC4); also elsewhere on the board
/micrcontroller/sel_t.1mA: U704.25 (PB1); also elsewhere on the board
/micrcontroller/sel_t.1uA: U704.26 (PB2); also elsewhere on the board
/micrcontroller/sel_t.10uA: U704.62 (PB9); also elsewhere on the board
/micrcontroller/sel_t.100uA: U704.60 (PB7); also elsewhere on the board
/micrcontroller/sel_v.1mA: U704.2 (PC13); also elsewhere on the board
/micrcontroller/sel_v.1uA: U704.58 (PB5); also elsewhere on the board
/micrcontroller/sel_v.10uA: U704.55 (PD2); also elsewhere on the board
/micrcontroller/sel_v.100uA: U704.57 (PB4); also elsewhere on the board
/micrcontroller/swclk: P701.4 (SWCLK), U704.50 (PA14)
/micrcontroller/swdio: P701.2 (SWDIO), U704.49 (PA13)
GNDPWR: C701.2, C702.2, C703.2, C704.2, C705.2, C706.2, C707.2, C708.2, C709.2, C710.2, C711.2, C712.2, C713.2, C714.2, C715.2, D702.1 (K), J701.1, J702.1, J703.A1 (GND), J703.A12 (GND), J703.B1 (GND), J703.B12 (GND), J704.4, P701.3 (GND), R701.1, R702.1, R703.1, SW701.3 (K), U701.7 (GND), U702.2 (G), U702.4 (G), U703.2 (GND), U704.15 (VSS), U704.27 (VSSA), U704.31 (VSS), U704.47 (VSS), U704.63 (VSS), U705.1 (GND); also elsewhere on the board
unnamed: D702.2 (A), R705.1

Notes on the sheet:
USB-C
Microcontroller (PAGE 7)
Level shifted SPI
POWER INDICATOR
IO expander port
USB PROGRAM BUTTON
RESET BUTTON
Microcontroller 3.3V
Solderable connector
st-link programmer
Level shifter so it can be used with an arduino
Reset and boot buttons for putting mcu into programming mode
Diode to prevent multiple pwr sources 5.1k resistors gives 5V @ 1amp per USB-C PD spec
28pf calculated using ecsxtal.com with 18pf load capacitance (from datasheet) and 4pf stray capacitance
Backup programmer if USB programming doesn't work
